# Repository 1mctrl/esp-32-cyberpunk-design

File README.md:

# ESP32 Cyberpunk Design

A custom PCB project based on the **ESP32-WROOM-32** module, designed with a cyberpunk-inspired aesthetic.  
All source files are created in **KiCad**.

---

## 📸 Gallery

### PCB 3D Render

### Gerber / CAM Preview

---
### Schema

## ⚡ Features
- Microcontroller: **ESP32-WROOM-32**
- Supply Voltage: 3.3V
- Interfaces: UART, SPI, I²C, GPIO
- Wi-Fi + Bluetooth connectivity
- Custom cyberpunk-style PCB layout

---

## 🚀 Getting Started
1. Open the project in **KiCad 7/8**.  
2. Inspect schematic and PCB design.  
3. Generate Gerbers for manufacturing if needed.  
4. Flash your firmware to the ESP32-WROOM-32 module.  

---

## 🛰️ Roadmap
- [ ] Add detailed BOM (Bill of Materials)  
- [ ] Upload firmware examples  
- [ ] Release manufacturing files as GitHub releases

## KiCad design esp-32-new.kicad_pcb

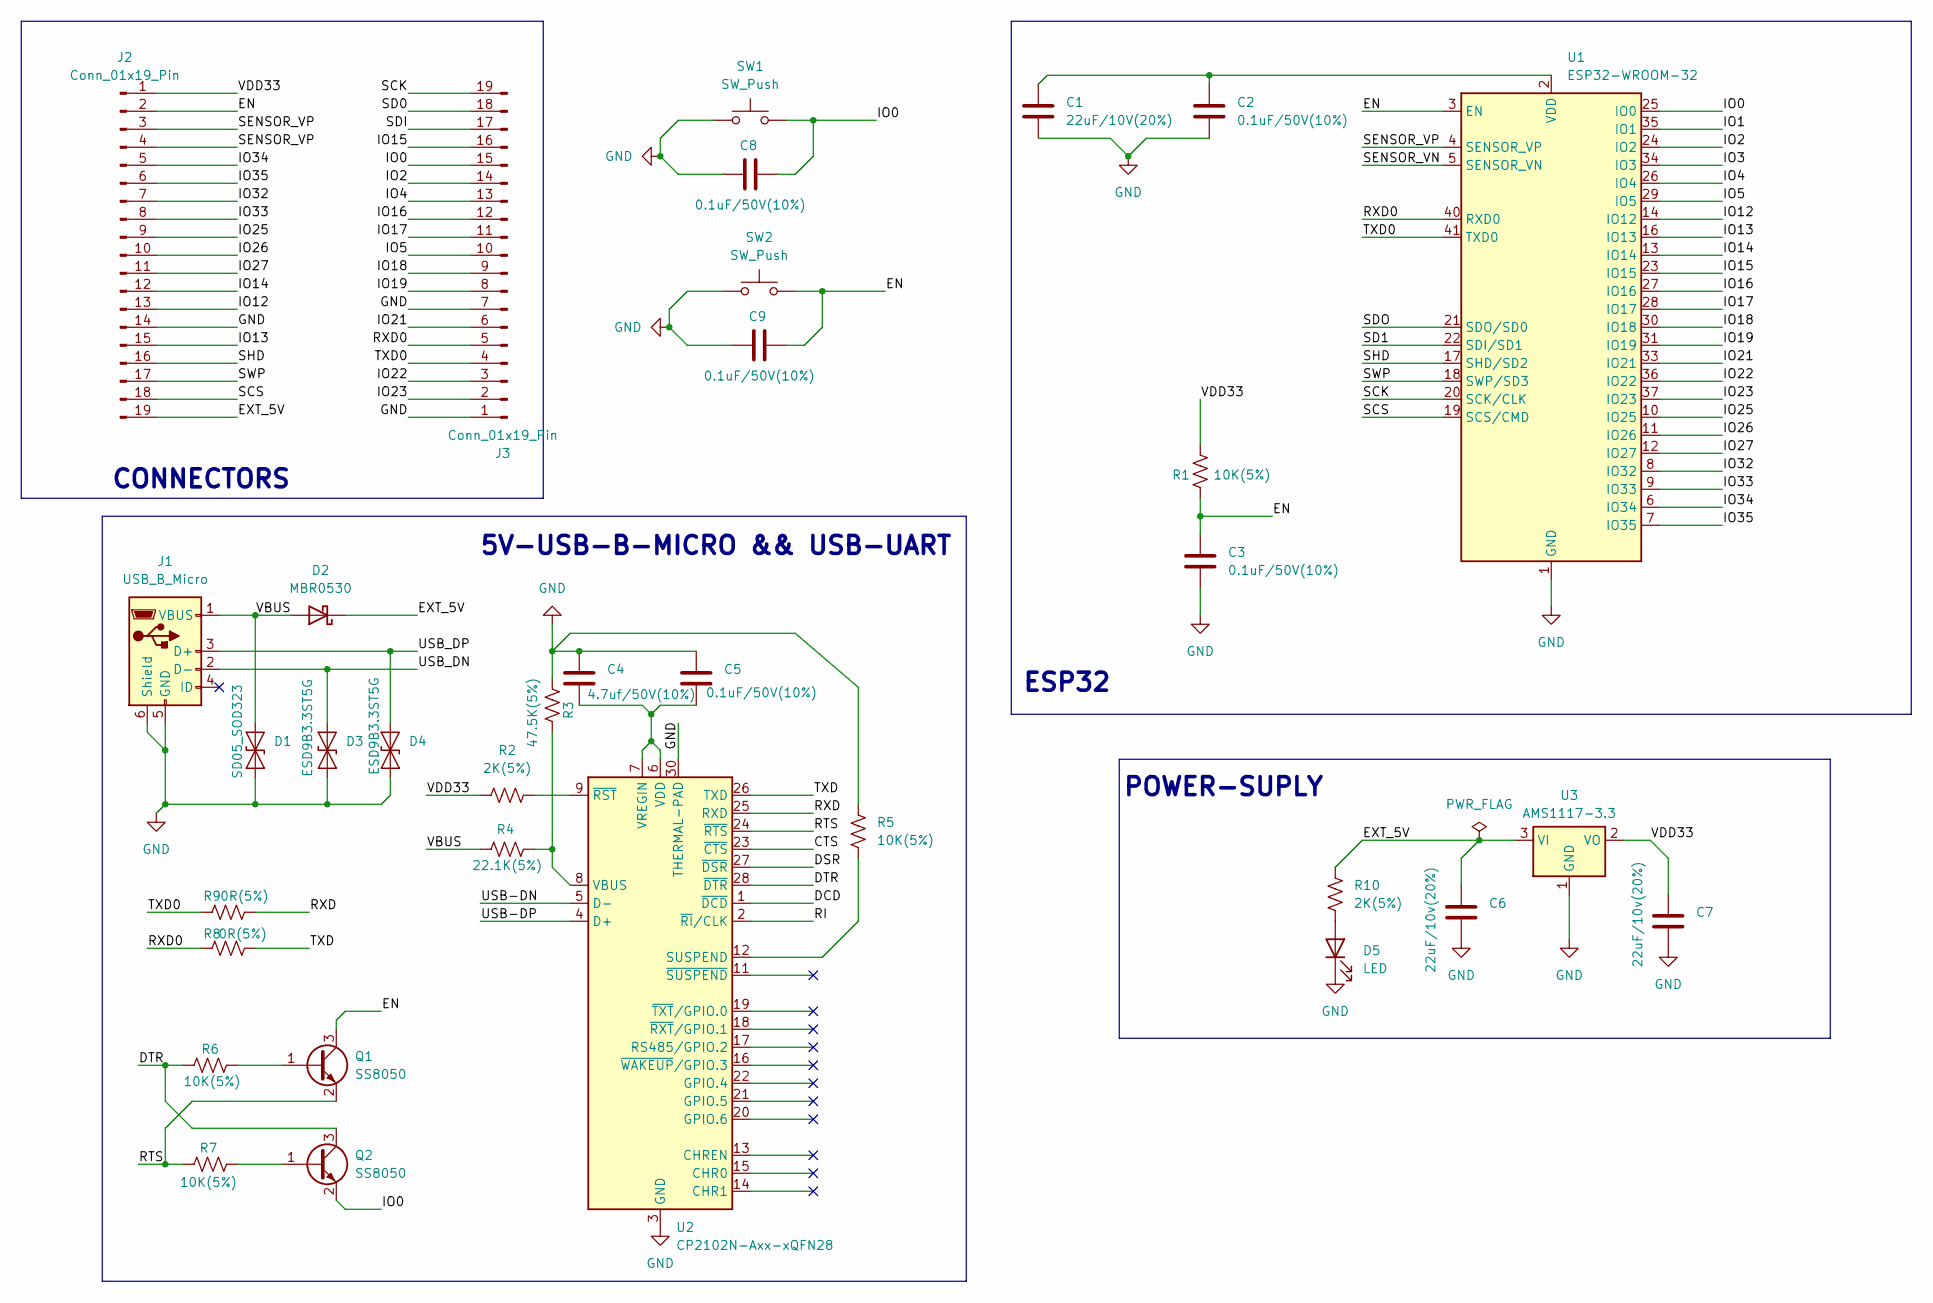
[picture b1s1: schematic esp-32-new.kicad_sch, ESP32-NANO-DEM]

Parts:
C1: 22uF/10V(20%); C_1206_3216Metric_Pad1.33x1.80mm_HandSolder
C2, C3, C5, C8, C9: 0.1uF/50V(10%); C_0402_1005Metric_Pad0.74x0.62mm_HandSolder
C4: 4.7uf/50V(10%); C_0805_2012Metric_Pad1.18x1.45mm_HandSolder
C6, C7: 22uF/10v(20%); C_1206_3216Metric_Pad1.33x1.80mm_HandSolder
D1: SD05_SOD323; D_SOD-323
D2: MBR0530; D_SOD-123
D3, D4: ESD9B3.3ST5G; D_SOD-923
D5: LED; LED_0603_1608Metric_Pad1.05x0.95mm_HandSolder
J1: USB_B_Micro; USB_Micro-B_Molex_47346-0001
J2, J3: Conn_01x19_Pin; PinHeader_1x19_P1.00mm_Horizontal
Q1, Q2: SS8050; SOT-23
R1, R5, R6, R7: 10K(5%); R_0603_1608Metric_Pad0.98x0.95mm_HandSolder
R2, R10: 2K(5%); R_0603_1608Metric_Pad0.98x0.95mm_HandSolder
R3: 47.5K(5%); R_0603_1608Metric_Pad0.98x0.95mm_HandSolder
R4: 22.1K(5%); R_0603_1608Metric_Pad0.98x0.95mm_HandSolder
R8, R9: 0R(5%); R_0603_1608Metric_Pad0.98x0.95mm_HandSolder
SW1, SW2: SW_Push; SW_SPST_B3U-1000P
U1: ESP32-WROOM-32
U2: CP2102N-Axx-xQFN28; QFN-28-1EP_5x5mm_P0.5mm_EP3.35x3.35mm
U3: AMS1117-3.3; SOT-223-3_TabPin2

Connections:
/CTS: U2.23 (~CTS)
/DCD: U2.1 (~DCD)
/DSR: U2.27 (~DSR)
/DTR: Q2.3 (C), R6.1, U2.28 (~DTR)
/EN: C3.1, C9.2, J2.2, Q1.3 (C), R1.2, SW2.2, U1.3 (EN)
/EXT_5V: C6.1, D2.1 (K), J2.19, R10.1, U3.3 (VI)
/IO0: C8.2, J3.15, Q2.2 (E), SW1.2, U1.25 (IO0)
/IO1: U1.35 (IO1)
/IO2: J3.14, U1.24 (IO2)
/IO3: U1.34 (IO3)
/IO4: J3.13, U1.26 (IO4)
/IO5: J3.10, U1.29 (IO5)
/IO12: J2.13, U1.14 (IO12)
/IO13: J2.15, U1.16 (IO13)
/IO14: J2.12, U1.13 (IO14)
/IO15: J3.16, U1.23 (IO15)
/IO16: J3.12, U1.27 (IO16)
/IO17: J3.11, U1.28 (IO17)
/IO18: J3.9, U1.30 (IO18)
/IO19: J3.8, U1.31 (IO19)
/IO21: J3.6, U1.33 (IO21)
/IO22: J3.3, U1.36 (IO22)
/IO23: J3.2, U1.37 (IO23)
/IO25: J2.9, U1.10 (IO25)
/IO26: J2.10, U1.11 (IO26)
/IO27: J2.11, U1.12 (IO27)
/IO32: J2.7, U1.8 (IO32)
/IO33: J2.8, U1.9 (IO33)
/IO34: J2.5, U1.6 (IO34)
/IO35: J2.6, U1.7 (IO35)
/RI: U2.2 (~RI/CLK)
/RTS: Q1.2 (E), R7.1, U2.24 (~RTS)
/RXD: R9.2, U2.25 (RXD)
/RXD0: J3.5, R8.1, U1.40 (RXD0)
/SCK: J3.19, U1.20 (SCK/CLK)
/SCS: J2.18, U1.19 (SCS/CMD)
/SD0: J3.18
/SD1: U1.22 (SDI/SD1)
/SDI: J3.17
/SDO: U1.21 (SDO/SD0)
/SENSOR_VN: U1.5 (SENSOR_VN)
/SENSOR_VP: J2.3, J2.4, U1.4 (SENSOR_VP)
/SHD: J2.16, U1.17 (SHD/SD2)
/SWP: J2.17, U1.18 (SWP/SD3)
/TXD: R8.2, U2.26 (TXD)
/TXD0: J3.4, R9.1, U1.41 (TXD0)
/USB-DN: U2.5 (D-)
/USB-DP: U2.4 (D+)
/USB_DN: D3.2 (A2), J1.2 (D-)
/USB_DP: D4.2 (A2), J1.3 (D+)
/VBUS: D1.2 (A2), D2.2 (A), J1.1 (VBUS), R4.1
/VDD33: C7.1, J2.1, R1.1, R2.1, U3.2 (VO)
GND: C1.2, C2.2, C3.2, C4.1, C5.1, C6.2, C7.2, C8.1, C9.1, D1.1 (A1), D3.1 (A1), D4.1 (A1), D5.1 (K), J1.5 (GND), J1.6 (Shield), J2.14, J3.1, J3.7, R3.1, R5.2, SW1.1, SW2.1, U1.1 (GND), U1.15 (GND), U1.38 (GND), U1.39 (GND), U2.3 (GND), U2.29 (GND), U2.30 (THERMAL-PAD), U3.1 (GND)
unnamed: D5.2 (A), R10.2
unnamed: Q1.1 (B), R6.2
unnamed: Q2.1 (B), R7.2
unnamed: C1.1, C2.1, U1.2 (VDD)
unnamed: R5.1, U2.12 (SUSPEND)
unnamed: R3.2, R4.2, U2.8 (VBUS)
unnamed: C4.2, C5.2, U2.6 (VDD), U2.7 (VREGIN)
unnamed: R2.2, U2.9 (~RST)

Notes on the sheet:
POWER-SUPLY
ESP32
5V-USB-B-MICRO && USB-UART
CONNECTORS

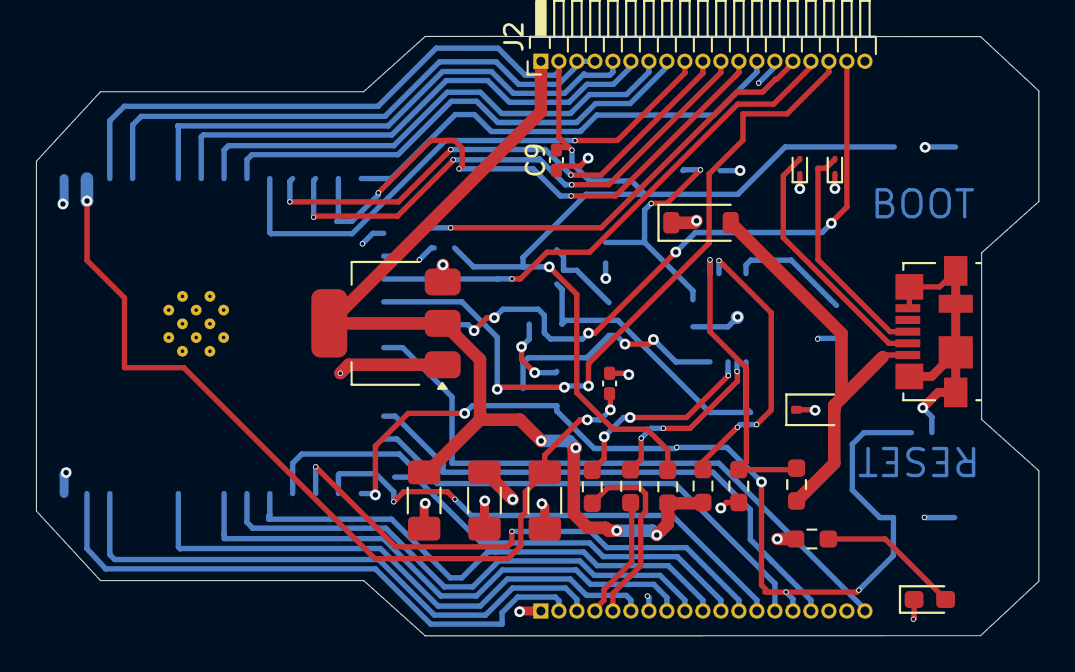
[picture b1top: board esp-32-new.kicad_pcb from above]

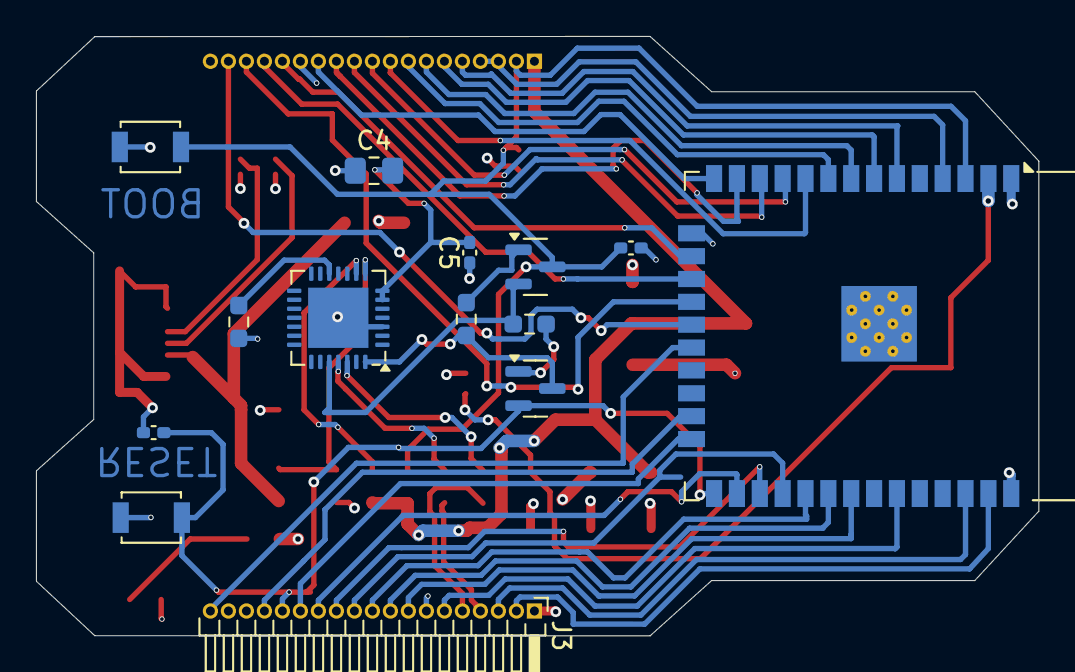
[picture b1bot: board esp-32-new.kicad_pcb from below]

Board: 4 copper layers, 55.7 x 33.3 mm, 34 parts (14 on the bottom side), 48 nets.

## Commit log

2025-08-25 first
2025-08-25 second
2025-08-25 esp32
